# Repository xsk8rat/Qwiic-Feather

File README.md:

# Qwiic-Feather
SparkFun's Qwiic on Adafruits Formated Board
Sparkfun has these great [boards with the Qwiic](https://www.sparkfun.com/categories/399) connectors for I2C.

Adafruit has the awesome system of [feather boards](https://www.adafruit.com/category/943) - which i use a lot.

# BOM (Parts List)

[Qwiic Connector Part](https://www.sparkfun.com/products/14417)

[Stacking Headers for Feather](https://www.adafruit.com/product/2830)

[Osh Park Board](https://oshpark.com/shared_projects/EL735FBY)

---
# Editorializing

An abomination against man and god.

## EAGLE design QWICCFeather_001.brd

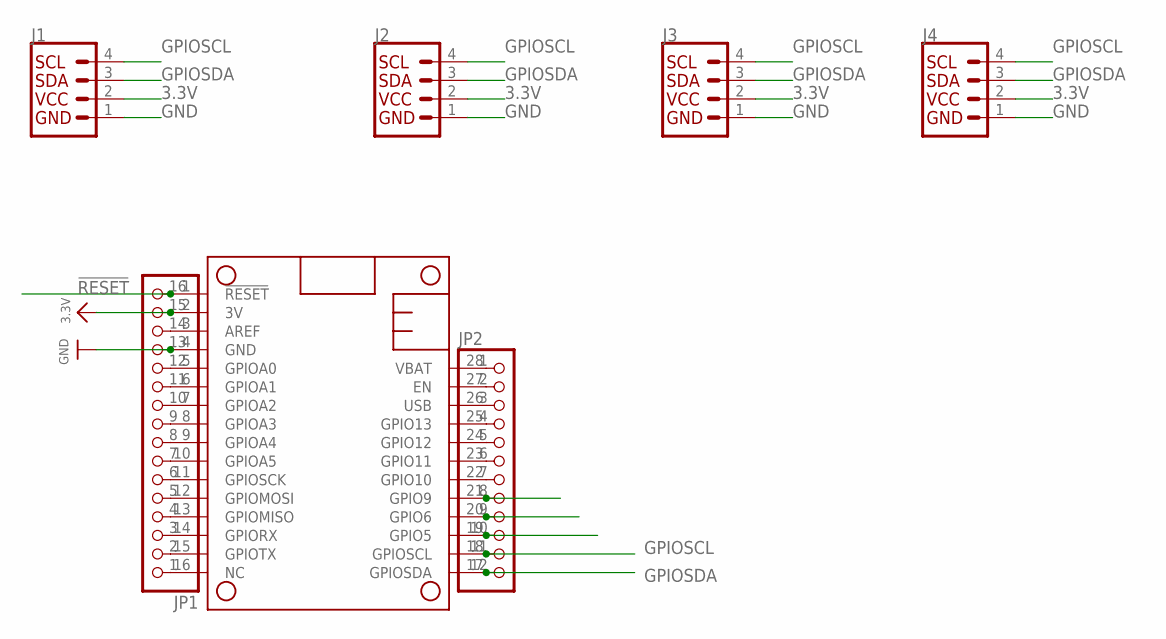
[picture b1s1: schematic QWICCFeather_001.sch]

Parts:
J1, J2, J3, J4: QWIIC_CONNECTORJS-1MM; 1X04_1MM_RA
JP1: HEADER-1X16ROUND; 1X16_ROUND
JP2: HEADER-1X12; 1X12_ROUND
MS1: FEATHERWING

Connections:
3.3V: J1.2 (VCC), J2.2 (VCC), J3.2 (VCC), J4.2 (VCC), JP1.15, MS1.2 (3V)
!RESET: JP1.16, MS1.1 (!RESET)
D5: JP2.10, MS1.19 (GPIO5)
D6: JP2.9, MS1.20 (GPIO6)
D9: JP2.8, MS1.21 (GPIO9)
GND: J1.1 (GND), J2.1 (GND), J3.1 (GND), J4.1 (GND), JP1.13, MS1.4 (GND)
GPIOSCL: J1.4 (SCL), J2.4 (SCL), J3.4 (SCL), J4.4 (SCL), JP2.11, MS1.18 (GPIOSCL)
GPIOSDA: J1.3 (SDA), J2.3 (SDA), J3.3 (SDA), J4.3 (SDA), JP2.12, MS1.17 (GPIOSDA)
unnamed: JP1.1, MS1.16 (NC)
unnamed: JP1.2, MS1.15 (GPIOTX)
unnamed: JP1.3, MS1.14 (GPIORX)
unnamed: JP1.4, MS1.13 (GPIOMISO)
unnamed: JP1.5, MS1.12 (GPIOMOSI)
unnamed: JP1.6, MS1.11 (GPIOSCK)
unnamed: JP1.7, MS1.10 (GPIOA5)
unnamed: JP1.8, MS1.9 (GPIOA4)
unnamed: JP1.9, MS1.8 (GPIOA3)
unnamed: JP1.10, MS1.7 (GPIOA2)
unnamed: JP1.11, MS1.6 (GPIOA1)
unnamed: JP1.12, MS1.5 (GPIOA0)
unnamed: JP1.14, MS1.3 (AREF)
unnamed: JP2.2, MS1.27 (EN)
unnamed: JP2.4, MS1.25 (GPIO13)
unnamed: JP2.5, MS1.24 (GPIO12)
unnamed: JP2.6, MS1.23 (GPIO11)
unnamed: JP2.7, MS1.22 (GPIO10)
USB: JP2.3, MS1.26 (USB)
VBAT: JP2.1, MS1.28 (VBAT)

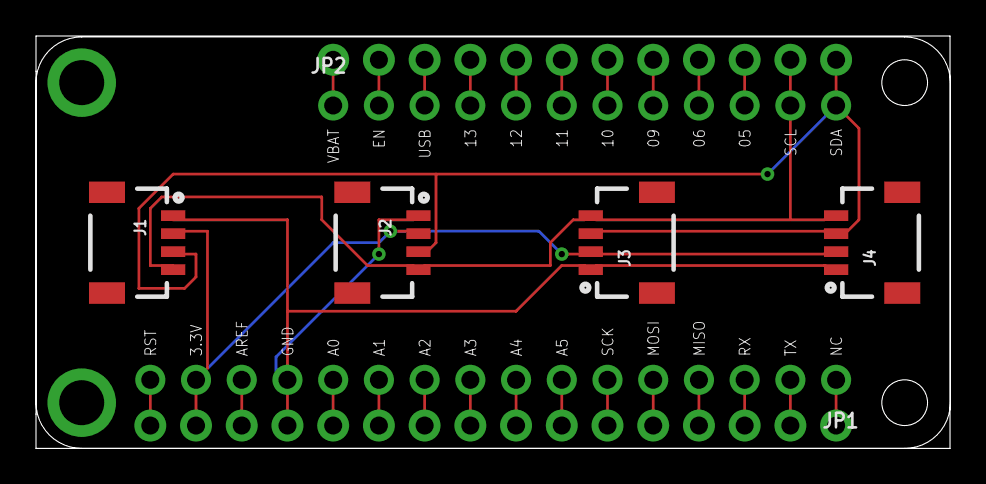
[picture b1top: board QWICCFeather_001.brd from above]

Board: 2 copper layers, 50.8 x 22.9 mm, 7 parts (0 on the bottom side), 28 nets.

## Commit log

2018-10-02 Adding Schematic and Board
    Rev 001
2018-10-02 Create README.md
    Added description from the OSHPark Page

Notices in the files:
parts and their libraries:
SparkFun-Connectors: Licensing: Creative Commons ShareAlike 4.0 International - https://creativecommons.org/licenses/by-sa/4.0
